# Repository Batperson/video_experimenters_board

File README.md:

# Video Experimenters Board
This is a circuit intended to facilitate experimentation with the ADV7184 video decoder and ADV7341 encoder, both from Analog Devices. 
It enables a microcontroller to display colour graphics over an NTSC or PAL video feed, by providing RGB and pixel-switch signals in sync with the video. Currently I am using this board as a basis for designing a colour OSD for multicopters and radio-controlled vehicles. See more about the project here: https://wekaosd.home.blog

To interface with the VEB you will need to do several things:
1. Provide regulated 1.8V and 3.3V power supplies
2. Program the 2 ICs using the I2C protocol via the SCK and SDA connectors. Programming scripts can be found at the Analog Devices website, or you can check the source for WekaOSD and see what I have done.
3. Feed the horizontal and vertical sync signals (HS and VS), and optionally odd/even field (FLD) and interrupt (INT) signals to your microcontroller. The microcontroller needs to lock to HS and VS, in order to send graphical output in sync with the video.
4. Generate RGB video signals, and use the fast-blank (FB) line to switch between the video feed and graphics as appropriate. RGB should be in the range of 0 - 0.7V. FB can be up to 3.3V. 
5. Connect an NTSC or PAL video source to one of the inputs, and a video monitor to one of the outputs. Component video output is also possible, and component video input should also work but I have not attempted to do so.

You will most likely want to implement a digital pixel bus with one or more bits allocated to each colour channel, and use a resistor divider to convert the digital signals to analogue RGB.

The STM32F4 series of microcontrollers are suitable microcontrollers, but any reasonably fast microcontroller should be capable. Given what has been achieved with the UzeBox project even an Arduino should be able to drive the VEB.

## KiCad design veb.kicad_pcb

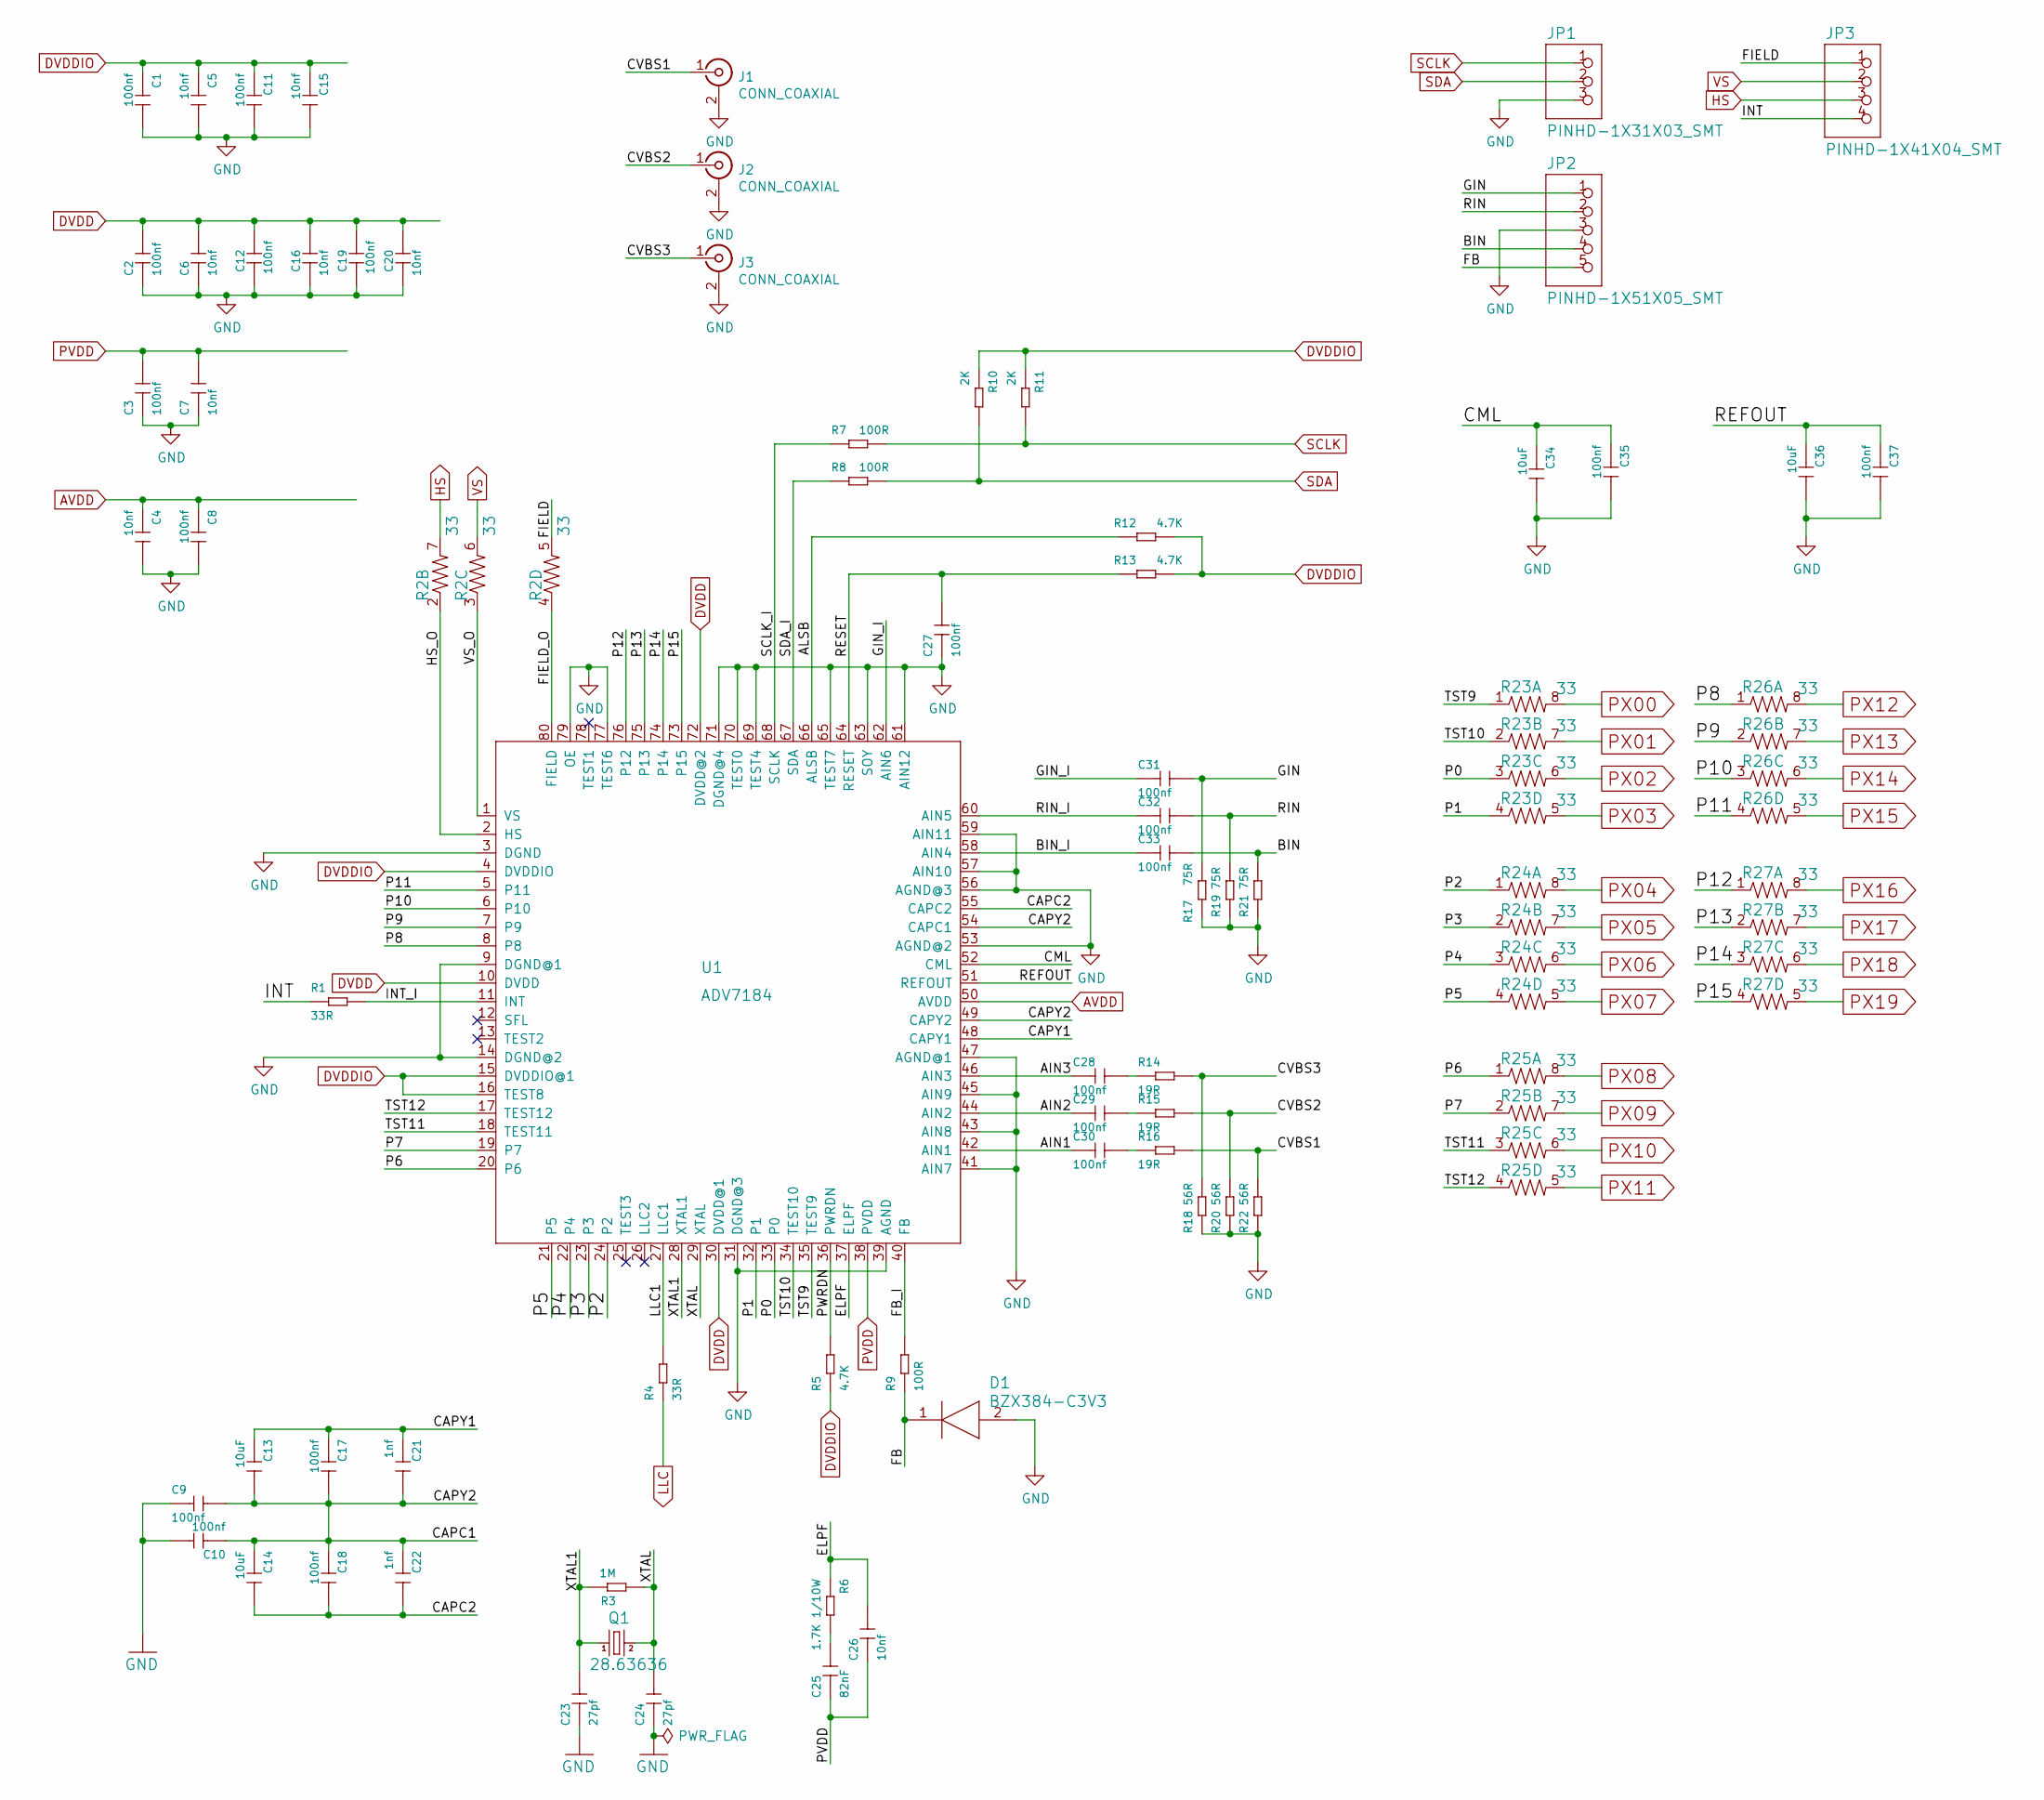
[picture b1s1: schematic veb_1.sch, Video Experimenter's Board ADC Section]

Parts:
C1, C2, C3, C8, C9, C10, C11, C12, C17, C18, C19, C27, C28, C29, C30, C31, C32, C33, C35, C37: 100nf; C0402
C4, C5, C6, C7, C15, C16, C20: 10nf; C0402
C13, C14, C34, C36: 10uF; C0805
C21, C22: 1nf; C0402
C23, C24: 27pf; C0402
C25: 82nF; C0805
C26: 10nf; C0805
D1: BZX384-C3V3; SOD2512X110N
J1, J2, J3: CONN_COAXIAL; RCA
JP1: PINHD-1X31X03_SMT; 1X03_SMT
JP2: PINHD-1X51X05_SMT; 1X05_SMT
JP3: PINHD-1X41X04_SMT; 1X04_SMT
Q1: 28.63636; HC49_S-SMD
R1, R4: 33R; R0603
R2, R23, R24, R25, R26, R27: 33; 0603-ARV
R3: 1M; R0603
R5, R12, R13: 4.7K; R0603
R6: 1.7K 1/10W; R0603
R7, R8, R9: 100R; R0603
R10, R11: 2K; R0603
R14, R15, R16: 19R; R0603
R17, R19, R21: 75R; R0603
R18, R20, R22: 56R; R0603
U1: ADV7184; LQFP80

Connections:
/veb_1/AIN1: C30.1, U1.42 (AIN1)
/veb_1/AIN2: C29.1, U1.44 (AIN2)
/veb_1/AIN3: C28.1, U1.46 (AIN3)
/veb_1/ALSB: R12.2, U1.66 (ALSB)
/veb_1/BIN: C33.2, JP2.4, R21.2
/veb_1/BIN_I: C33.1, U1.58 (AIN4)
/veb_1/CAPC1: C9.2, C10.1, C13.2, C14.1, C17.2, C18.1, C21.2, C22.1, U1.49 (CAPY2), U1.54 (CAPC1)
/veb_1/CAPC2: C14.2, C18.2, C22.2, U1.55 (CAPC2)
/veb_1/CAPY1: C13.1, C17.1, C21.1, U1.48 (CAPY1)
/veb_1/CML: C34.1, C35.1, U1.52 (CML)
/veb_1/CVBS1: J1.1 (In), R16.2, R22.2
/veb_1/CVBS2: J2.1 (In), R15.2, R20.2
/veb_1/CVBS3: J3.1 (In), R14.2, R18.2
/veb_1/ELPF: C26.2, R6.1, U1.37 (ELPF)
/veb_1/FB: D1.1 (K), JP2.5, R9.1
/veb_1/FB_I: R9.2, U1.40 (FB)
/veb_1/FIELD: JP3.1, R2.5 (2)
/veb_1/FIELD_O: R2.4 (1), U1.80 (FIELD)
/veb_1/GIN: C31.2, JP2.1, R17.1
/veb_1/GIN_I: C31.1, U1.62 (AIN6)
/veb_1/HS_O: R2.2 (1), U1.2 (HS)
/veb_1/INT: JP3.4, R1.1
/veb_1/INT_I: R1.2, U1.11 (INT)
/veb_1/LLC1: R4.2, U1.27 (LLC1)
/veb_1/P0: R23.3 (1), U1.33 (P0)
/veb_1/P1: R23.4 (1), U1.32 (P1)
/veb_1/P2: R24.1, U1.24 (P2)
/veb_1/P3: R24.2 (1), U1.23 (P3)
/veb_1/P4: R24.3 (1), U1.22 (P4)
/veb_1/P5: R24.4 (1), U1.21 (P5)
/veb_1/P6: R25.1, U1.20 (P6)
/veb_1/P7: R25.2 (1), U1.19 (P7)
/veb_1/P8: R26.1, U1.8
/veb_1/P9: R26.2 (1), U1.7 (P9)
/veb_1/P10: R26.3 (1), U1.6 (P10)
/veb_1/P11: R26.4 (1), U1.5 (P11)
/veb_1/P12: R27.1, U1.76 (P12)
/veb_1/P13: R27.2 (1), U1.75 (P13)
/veb_1/P14: R27.3 (1), U1.74 (P14)
/veb_1/P15: R27.4 (1), U1.73 (P15)
/veb_1/PWRDN: R5.2, U1.36 (PWRDN)
/veb_1/REFOUT: C36.1, C37.1, U1.51 (REFOUT)
/veb_1/RESET: C27.2, R13.2, U1.64 (RESET)
/veb_1/RIN: C32.2, JP2.2, R19.2
/veb_1/RIN_I: C32.1, U1.60 (AIN5)
/veb_1/SCLK_I: R7.1, U1.68 (SCLK)
/veb_1/SDA_I: R8.1, U1.67 (SDA)
/veb_1/TST9: R23.1, U1.35 (TEST9)
/veb_1/TST10: R23.2 (1), U1.34 (TEST10)
/veb_1/TST11: R25.3 (1), U1.18 (TEST11)
/veb_1/TST12: R25.4 (1), U1.17 (TEST12)
/veb_1/VS_O: R2.3 (1), U1.1 (VS)
/veb_1/XTAL: C24.2, Q1.2, R3.1, U1.29 (XTAL)
/veb_1/XTAL1: C23.2, Q1.1, R3.2, U1.28 (XTAL1)
AVDD: C4.1, C8.1, U1.50 (AVDD); also elsewhere on the board
DVDD: C2.2, C6.2, C12.1, C16.1, C19.1, C20.1, U1.10 (DVDD), U1.30 (DVDD@1), U1.72 (DVDD@2); also elsewhere on the board
DVDDIO: C1.1, C5.1, C11.1, C15.1, R5.1, R10.1, R11.1, R12.1, R13.1, U1.4 (DVDDIO), U1.15 (DVDDIO@1), U1.16 (TEST8); also elsewhere on the board
GND: C1.2, C2.1, C3.1, C4.2, C5.2, C6.1, C7.1, C8.2, C9.1, C10.2, C11.2, C12.2, C15.2, C16.2, C19.2, C20.2, C23.1, C24.1, C27.1, C34.2, C35.2, C36.2, C37.2, D1.2 (A), J1.2 (Ext), J2.2 (Ext), J3.2 (Ext), JP1.3, JP2.3, R17.2, R18.1, R19.1, R20.1, R21.1, R22.1, U1.3 (DGND), U1.9 (DGND@1), U1.14 (DGND@2), U1.31 (DGND@3), U1.39 (AGND), U1.41 (AIN7), U1.43 (AIN8), U1.45 (AIN9), U1.47 (AGND@1), U1.53 (AGND@2), U1.56 (AGND@3), U1.57 (AIN10), U1.59 (AIN11), U1.61 (AIN12), U1.63 (SOY), U1.65 (TEST7), U1.69 (TEST4), U1.70 (TEST0), U1.71 (DGND@4), U1.77 (TEST6), U1.79 (OE); also elsewhere on the board
HS: JP3.3, R2.7 (2); also elsewhere on the board
LLC: R4.1; also elsewhere on the board
unnamed: C25.2, R6.2
unnamed: C28.2, R14.1
unnamed: C29.2, R15.1
unnamed: C30.2, R16.1
PVDD: C3.2, C7.2, C25.1, C26.1, U1.38 (PVDD); also elsewhere on the board
PX00: R23.8 (2); also elsewhere on the board
PX01: R23.7 (2); also elsewhere on the board
PX02: R23.6 (2); also elsewhere on the board
PX03: R23.5 (2); also elsewhere on the board
PX04: R24.8 (2); also elsewhere on the board
PX05: R24.7 (2); also elsewhere on the board
PX06: R24.6 (2); also elsewhere on the board
PX07: R24.5 (2); also elsewhere on the board
PX08: R25.8 (2); also elsewhere on the board
PX09: R25.7 (2); also elsewhere on the board
PX10: R25.6 (2); also elsewhere on the board
PX11: R25.5 (2); also elsewhere on the board
PX12: R26.8 (2); also elsewhere on the board
PX13: R26.7 (2); also elsewhere on the board
PX14: R26.6 (2); also elsewhere on the board
PX15: R26.5 (2); also elsewhere on the board
PX16: R27.8 (2); also elsewhere on the board
PX17: R27.7 (2); also elsewhere on the board
PX18: R27.6 (2); also elsewhere on the board
PX19: R27.5 (2); also elsewhere on the board
SCLK: JP1.1, R7.2, R11.2; also elsewhere on the board
SDA: JP1.2, R8.2, R10.2; also elsewhere on the board
VS: JP3.2, R2.6 (2); also elsewhere on the board

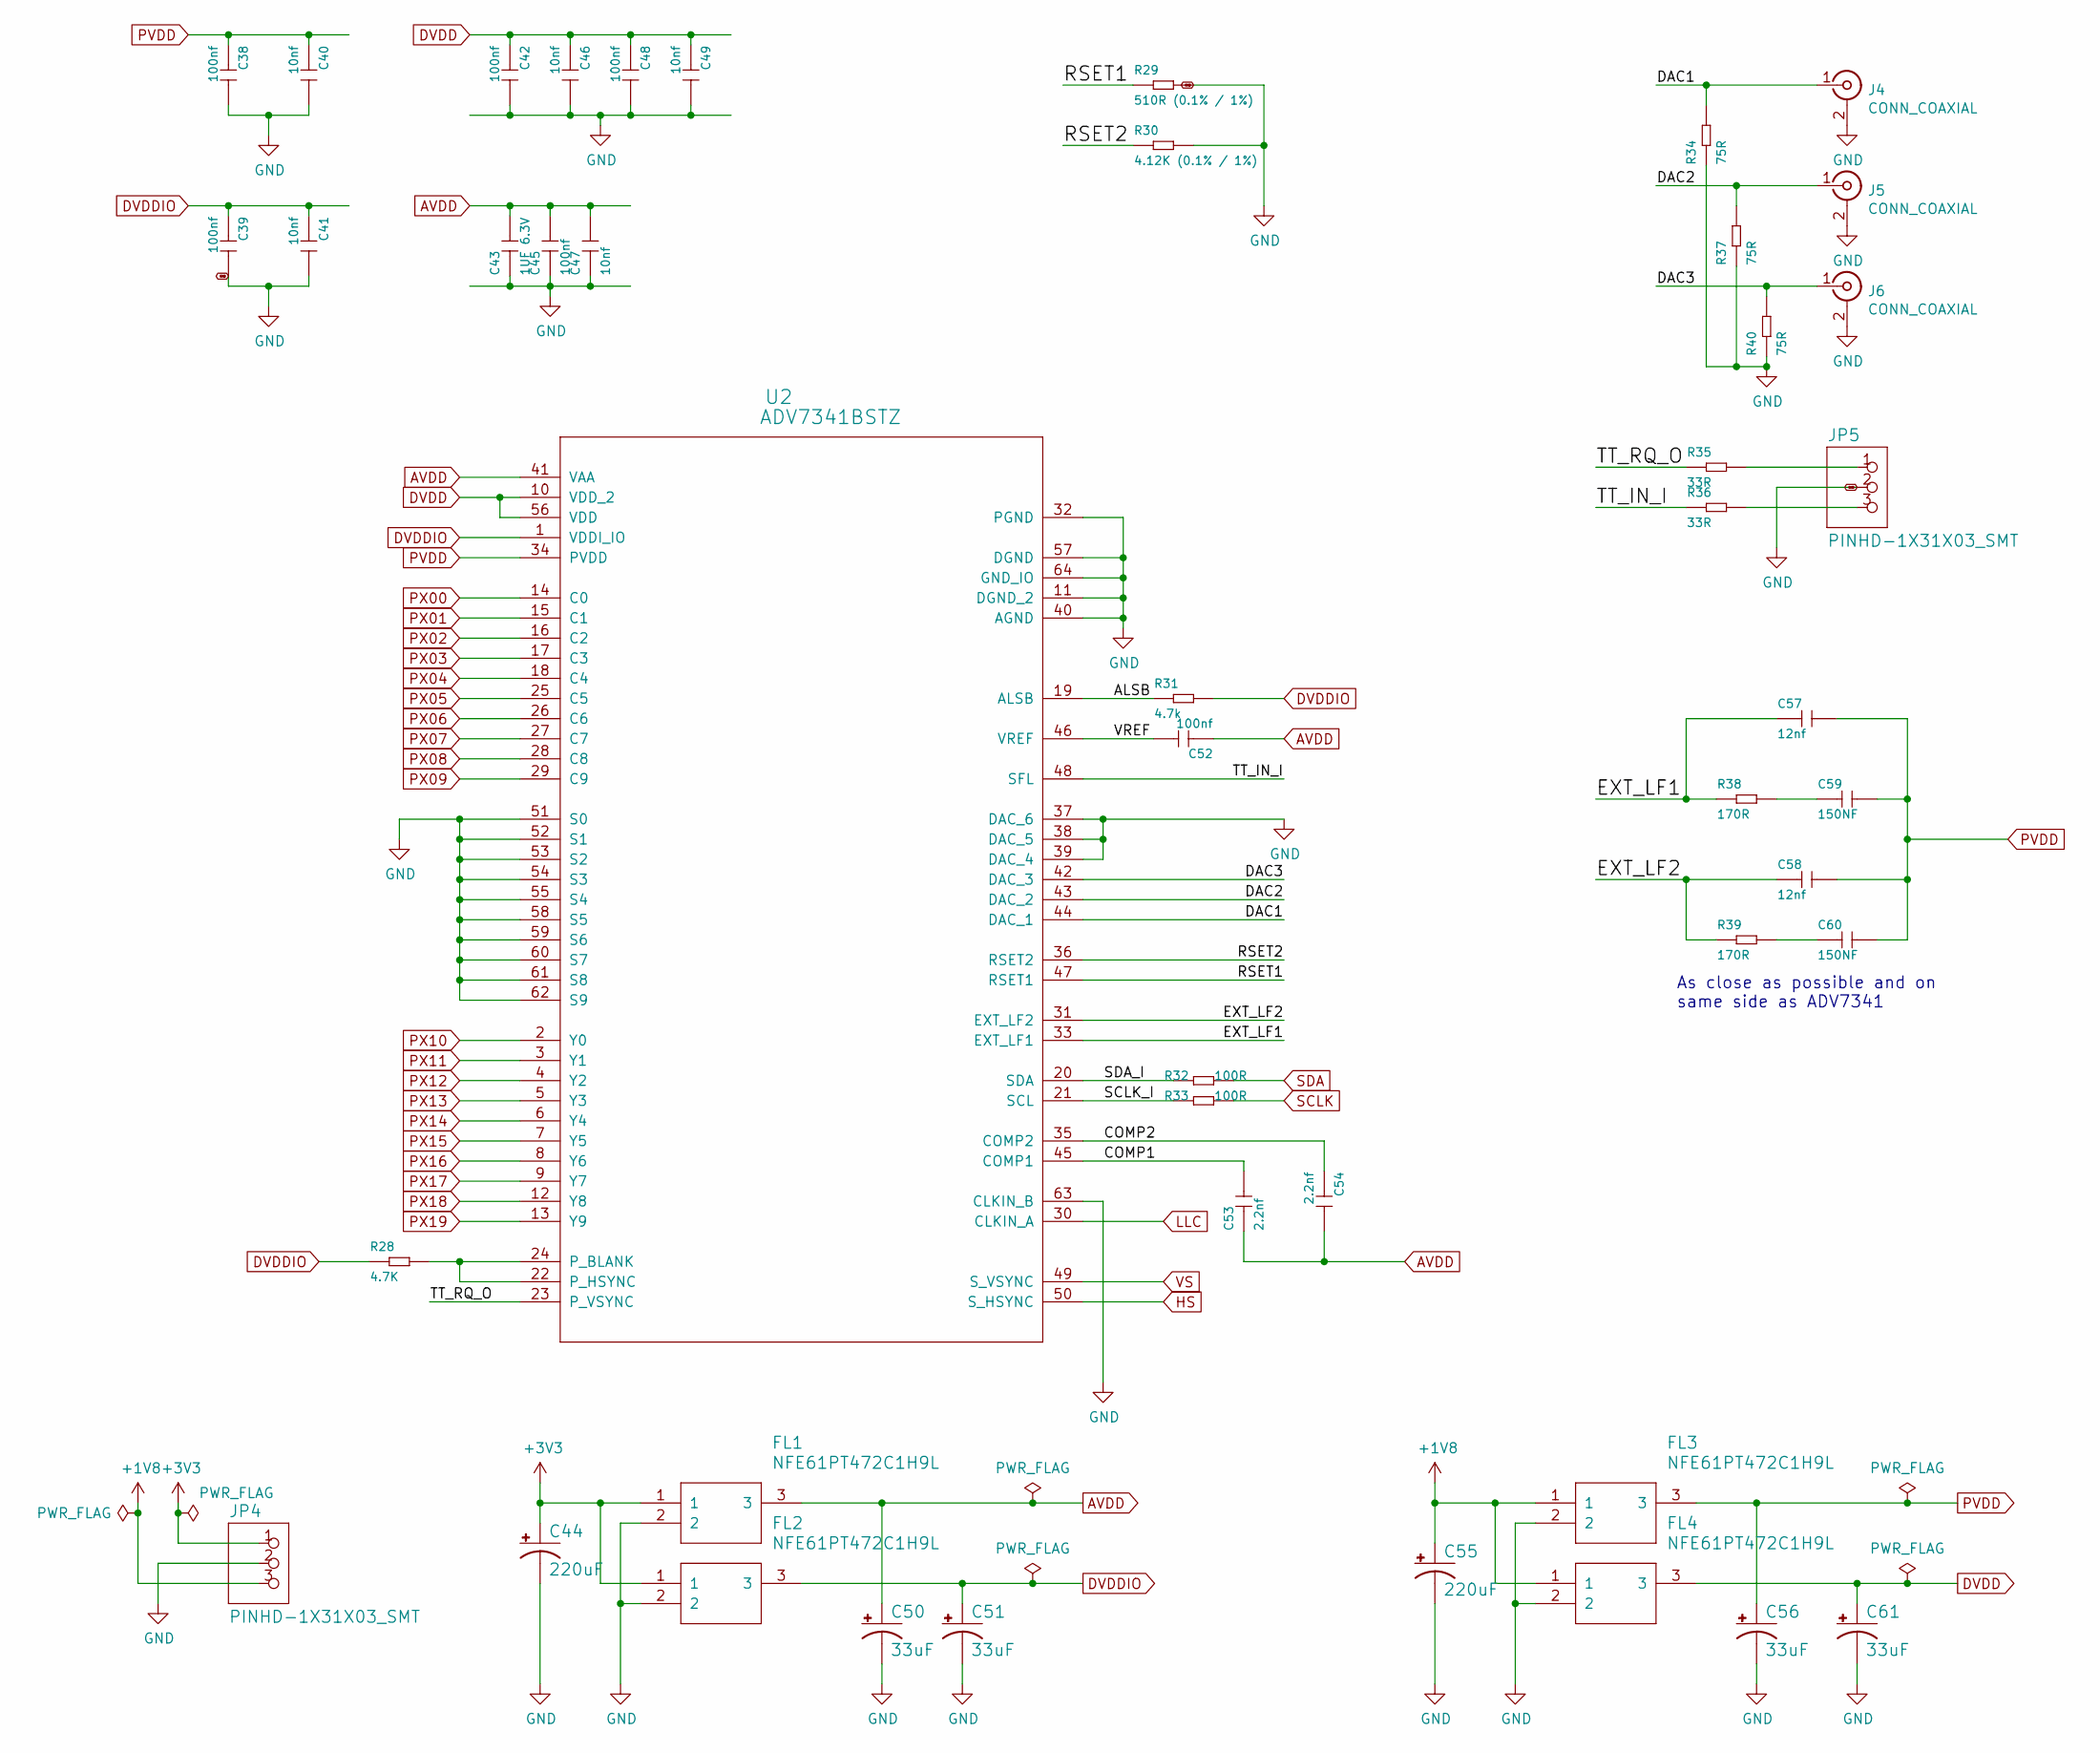
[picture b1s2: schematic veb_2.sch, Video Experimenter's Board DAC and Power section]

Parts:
C38, C39, C42, C45, C48, C52: 100nf; C0402
C40, C41, C46, C47, C49: 10nf; C0402
C43: 1UF 6.3V; C0402
C44, C55: 220uF; CPOL-RADIAL-100UF-25V
C50, C51, C56, C61: 33uF; EIA3528
C53, C54: 2.2nf; C0402
C57, C58: 12nf; C0402
C59, C60: 150NF; C0402
FL1, FL2, FL3, FL4: NFE61PT472C1H9L; 6816
J4, J5, J6: CONN_COAXIAL; RCA
JP4, JP5: PINHD-1X31X03_SMT; 1X03_SMT
R28: 4.7K; R0603
R29: 510R (0.1% / 1%); R0603
R30: 4.12K (0.1% / 1%); R0603
R31: 4.7k; R0603
R32, R33: 100R; R0603
R34, R37, R40: 75R; R0603
R35, R36: 33R; R0603
R38, R39: 170R; R0603
U2: ADV7341BSTZ; ST_64_2

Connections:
+1V8: C55.1 (+), FL3.1, FL4.1, JP4.3
+3V3: C44.1 (+), FL1.1, FL2.1, JP4.1
/veb_2/ALSB: R31.1, U2.19 (ALSB)
/veb_2/COMP1: C53.2, U2.45 (COMP1)
/veb_2/COMP2: C54.1, U2.35 (COMP2)
/veb_2/DAC1: J4.1 (In), R34.2, U2.44 (DAC_1)
/veb_2/DAC2: J5.1 (In), R37.2, U2.43 (DAC_2)
/veb_2/DAC3: J6.1 (In), R40.2, U2.42 (DAC_3)
/veb_2/EXT_LF1: C57.1, R38.1, U2.33 (EXT_LF1)
/veb_2/EXT_LF2: C58.1, R39.1, U2.31 (EXT_LF2)
/veb_2/RSET1: R29.1, U2.47 (RSET1)
/veb_2/RSET2: R30.1, U2.36 (RSET2)
/veb_2/SCLK_I: R33.1, U2.21 (SCL)
/veb_2/SDA_I: R32.1, U2.20 (SDA)
/veb_2/TT_IN_I: R36.1, U2.48 (SFL)
/veb_2/TT_RQ_O: R35.1, U2.23 (P_VSYNC)
/veb_2/VREF: C52.2, U2.46 (VREF)
AVDD: C43.2, C45.2, C47.2, C50.A (+), C52.1, C53.1, C54.2, FL1.3, U2.41 (VAA); also elsewhere on the board
DVDD: C42.1, C46.1, C48.1, C49.1, C61.A (+), FL4.3, U2.10 (VDD_2), U2.56 (VDD); also elsewhere on the board
DVDDIO: C39.1, C41.1, C51.A (+), FL2.3, R28.1, R31.2, U2.1 (VDDI_IO); also elsewhere on the board
GND: C38.2, C39.2, C40.2, C41.2, C42.2, C43.1, C44.2 (-), C45.1, C46.2, C47.1, C48.2, C49.2, C50.C (-), C51.C (-), C55.2 (-), C56.C (-), C61.C (-), FL1.2, FL2.2, FL3.2, FL4.2, J4.2 (Ext), J5.2 (Ext), J6.2 (Ext), JP4.2, JP5.2, R29.2, R30.2, R34.1, R37.1, R40.1, U2.11 (DGND_2), U2.32 (PGND), U2.37 (DAC_6), U2.38 (DAC_5), U2.39 (DAC_4), U2.40 (AGND), U2.51 (S0), U2.52 (S1), U2.53 (S2), U2.54 (S3), U2.55 (S4), U2.57 (DGND), U2.58 (S5), U2.59 (S6), U2.60 (S7), U2.61 (S8), U2.62 (S9), U2.63 (CLKIN_B), U2.64 (GND_IO); also elsewhere on the board
HS: U2.50 (S_HSYNC); also elsewhere on the board
LLC: U2.30 (CLKIN_A); also elsewhere on the board
unnamed: C59.1, R38.2
unnamed: C60.1, R39.2
unnamed: JP5.1, R35.2
unnamed: JP5.3, R36.2
unnamed: R28.2, U2.22 (P_HSYNC), U2.24 (P_BLANK)
PVDD: C38.1, C40.1, C56.A (+), C57.2, C58.2, C59.2, C60.2, FL3.3, U2.34 (PVDD); also elsewhere on the board
PX00: U2.14 (C0); also elsewhere on the board
PX01: U2.15 (C1); also elsewhere on the board
PX02: U2.16 (C2); also elsewhere on the board
PX03: U2.17 (C3); also elsewhere on the board
PX04: U2.18 (C4); also elsewhere on the board
PX05: U2.25 (C5); also elsewhere on the board
PX06: U2.26 (C6); also elsewhere on the board
PX07: U2.27 (C7); also elsewhere on the board
PX08: U2.28 (C8); also elsewhere on the board
PX09: U2.29 (C9); also elsewhere on the board
PX10: U2.2 (Y0); also elsewhere on the board
PX11: U2.3 (Y1); also elsewhere on the board
PX12: U2.4 (Y2); also elsewhere on the board
PX13: U2.5 (Y3); also elsewhere on the board
PX14: U2.6 (Y4); also elsewhere on the board
PX15: U2.7 (Y5); also elsewhere on the board
PX16: U2.8 (Y6); also elsewhere on the board
PX17: U2.9 (Y7); also elsewhere on the board
PX18: U2.12 (Y8); also elsewhere on the board
PX19: U2.13 (Y9); also elsewhere on the board
SCLK: R33.2; also elsewhere on the board
SDA: R32.2; also elsewhere on the board
VS: U2.49 (S_VSYNC); also elsewhere on the board

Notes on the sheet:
As close as possible and on same side as ADV7341

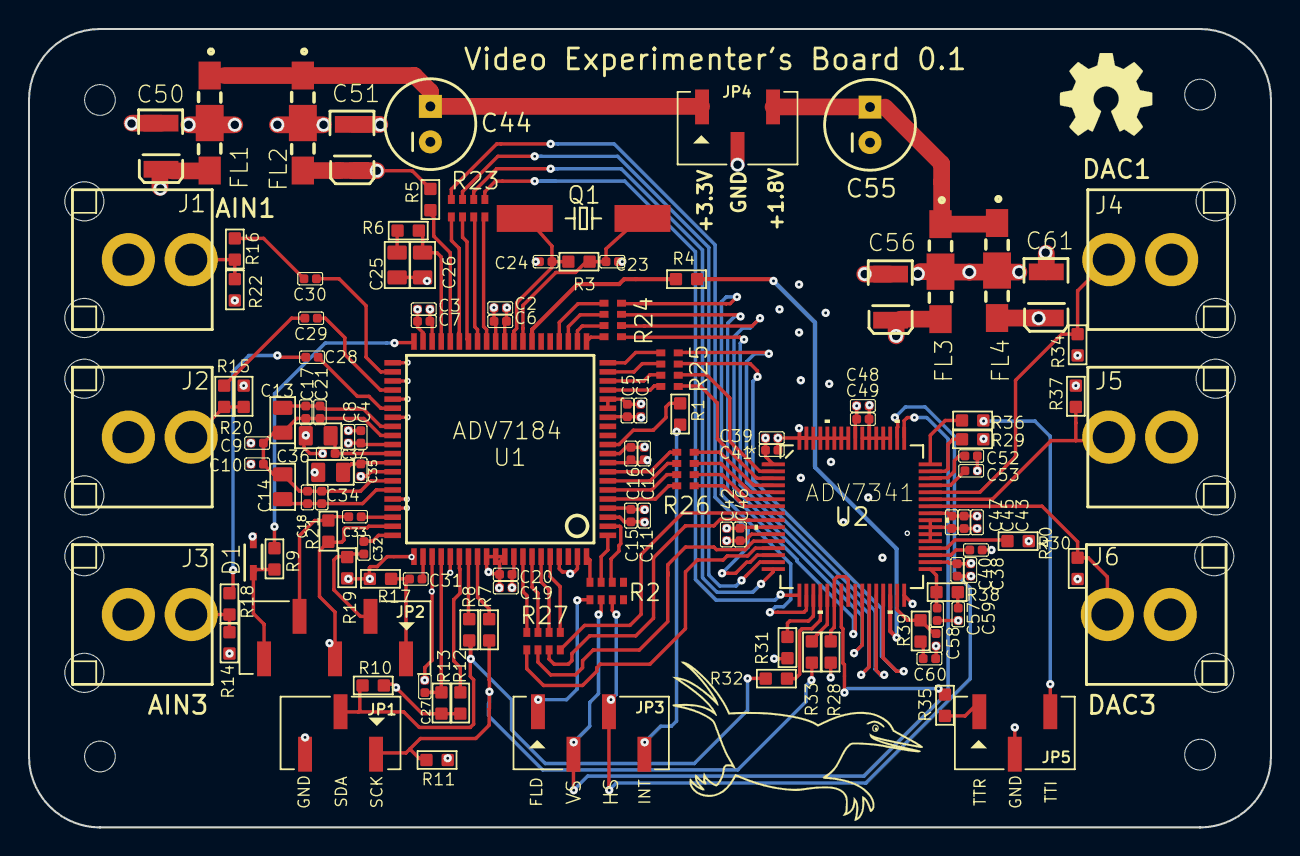
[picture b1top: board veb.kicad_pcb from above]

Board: 4 copper layers, 88.9 x 57.2 mm, 120 parts (0 on the bottom side), 110 nets.
